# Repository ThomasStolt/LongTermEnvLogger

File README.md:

# Long Term Environment Logger

The aim of this project is to measure, store, display and evaluate the temperature in the rooms of a large building over an extended time period. This project has 2 main components:

A. The hardware of the sensor.

B. The server infrastructure to receive, store and display the measurements.

## The Hardware

1. An ultra-low power timer circuit that uses nano-Amps only when asleep and wakes up the entire circuit every approx. 5 minutes for measurement.

2. An LDO voltage regulator that regulates the incoming battery voltage from a LiIon battery to 3.3V

3. A battery voltage sensor that sends the battery voltage to the ESP8266 ADC pin with a voltage divider so that the battery voltage can be monitored.

4. The ESP8266 with a DS18B20 temperature sensor.

5. A small solar cell with a charging circuit, to keep the battery charged for as long as possible.

... and some additional mechanical and electronic components.

The ESP8266 was chosen as the microcontroller. It is versatile, very affordable, has more than enough functionality and information is easy to find.

If you think about it in detail, this project is not quite as trivial as it first appears. Some of the things to consider are:

* Runtime - How long does a single battery last?

  * As the battery-operated temperature sensors are to be distributed throughout a very large building, you want the individual sensors to run for as long as possible, so that you don't have to run around the building changing or charging batteries all the time. One option is the energy-saving mode ("DeepSleep") of the microcontroller. This would reduce the current draw during deep sleep to about 14µA. However, we want to achieve sleep current of less than 100nA! So, the normal Deep-Sleep will not do it.

* Update OTA(?)
	* It might be worth considering adding this capability. This would probably affect the runtime as well, because if we check for updates every time the circuit wakes up, it will cost runtime and energy. So, the question here is, how much runtime this would cost and is this really necessary?

* WiFi Connection Time
	* When the ESP8266 wakes up and has WiFi switched on, it draws about 70mA, which is a lot. So, all efforts need to be taken to reduce the connection time to be a short as possible.

* Power supply / battery
	* Li-Ion batteries are a good energy source for this type of project, especially the 18650 type. They are relatively inexpensive for their capacity. However, as these batteries are very sensitive to mishandling, it is important to take appropriate precautions.
		* How can you ensure that the LiIon battery will not be deep discharged?
		* How can I ensure that the LiIon battery cannot be overcharged?
		* How can I monitor the voltage of the power supply (of the LiIo battery) in order to replace or charge the battery in good time?
		* All batteries must be checked regularly for their capacity and possible health issues.

## Overview

First a short diagram for an overview:

---

## Programmer Tool

An interactive TUI (terminal user interface) that programs each sensor in two steps. Built with [Textual](https://textual.textualize.io/) for a comfortable dark-mode interface.

### Features

- Auto-detects USB serial ports (OTA/network ports filtered out) and pre-selects the right one
- Live hotplug detection — plug in the adapter and it appears immediately
- Parallel background compilation while you prepare the hardware
- Auto-selects the WiFi network from your credentials file (strongest signal)
- Two-column credentials panel — file list on the left, network config on the right; press `E` to edit
- Per-location sensor registry (`sensors_home.csv`, `sensors_school.csv`, …) — switches automatically with the selected credentials file
- Always-visible Serial Debug panel showing raw ESP output during setup-sketch read
- Adjustable baud rate selector and automatic retry loop on serial read timeout
- Full keyboard navigation — no mouse required
- Clean two-step workflow with progress feedback

### Prerequisites

- [arduino-cli](https://arduino.github.io/arduino-cli/) with the ESP8266 core installed:
  ```bash
  arduino-cli core install esp8266:esp8266
  ```
- Python 3.10+
  ```bash
  pip install -r tool/requirements.txt
  ```

### Credentials Setup

```bash
cp credentials.example.h credentials_Home.h
# Edit credentials_Home.h and fill in your SSID and password
```

You can have multiple credential files for different locations:
- `credentials_Home.h`
- `credentials_School.h`

These files are gitignored — never commit real credentials.

### Board Configuration

Edit `tool/arduino_config.py` if needed:
```python
BOARD_FQBN = "esp8266:esp8266:generic"  # change for your ESP8266 variant
```

Common FQBNs:
- `esp8266:esp8266:generic` — bare ESP-01/ESP-12 modules
- `esp8266:esp8266:nodemcuv2` — NodeMCU v2 / Lolin
- `esp8266:esp8266:d1_mini` — Wemos D1 Mini

### Running the Tool

Connect the ESP8266 via USB-TTL adapter, then:

```bash
cd tool && python3 ltl_programmer.py
```

**Keyboard shortcuts:**

| Key | Action |
|-----|--------|
| `F` | Start flash workflow |
| `R` | Refresh port list |
| `E` | Edit network config for selected credentials |
| `Q` | Quit |
| `Enter` | Confirm / Continue |

**Workflow:**

1. Select your USB-TTL adapter port (pre-selected automatically)
2. Select the credentials location (Home, School, …)
3. Press `F` to start — the tool guides you through:
   - Enter flash mode (RST + FLASH button sequence)
   - Setup sketch uploads and reads MAC address, DS18B20 address, and nearby WiFi
   - WiFi network is auto-selected from your credentials file
   - Enter a room number (1–254)
   - Production firmware compiles and uploads with all values baked in
4. Sensor is recorded in `tool/sensors_<location>.csv` (one file per credentials location)

### Flash Mode (ESP-12 / bare modules)

Bare ESP8266 modules without an auto-reset circuit require manual flash mode entry:

1. Press and hold **RST**
2. Press and hold **FLASH**
3. Release **RST**
4. Release **FLASH**

The tool will prompt you at the right moment.

### Manual Flash Fallback

If arduino-cli is not available, you can flash manually using the Arduino IDE:

1. Flash `code/LTL_setup/LTL_setup.ino` and open Serial Monitor at 115200 baud
2. Note the MAC address and DS18B20 address
3. Edit `code/LTL_sensor/LTL_sensor.ino` — replace the placeholder values
4. Copy your `credentials_<location>.h` to `credentials.h` in the same folder
5. Flash `code/LTL_sensor/LTL_sensor.ino`

### Sensor Registry

`tool/sensors_<location>.csv` tracks all programmed sensors per location (gitignored). For example, `sensors_home.csv` and `sensors_school.csv` are created automatically when you first flash a sensor using that credentials file.

| Field | Description |
|---|---|
| timestamp | When the sensor was programmed |
| room_number | Room number (also last IP octet) |
| mac_address | ESP8266 MAC address |
| ds18b20_address | DS18B20 OneWire address |
| location | Credentials location used |
| ssid | WiFi network name |
| bssid | Pinned BSSID (empty if not pinned) |
| channel | Pinned channel (empty if not pinned) |

### Battery Life Optimization

The production firmware (`code/LTL_sensor/LTL_sensor.ino`) reduces ESP8266 awake time by ~1060–1480ms per 5-minute cycle compared to the original firmware:

| Optimization | Saving |
|---|---|
| 9-bit DS18B20 resolution (±0.5°C) + async overlap | ~750ms |
| Hardcoded DS18B20 address (no bus scan) | ~10–30ms |
| Post-publish delays removed | ~300ms |
| **Total without BSSID pinning** | **~1060–1080ms** |
| Optional BSSID/channel pinning | +~200–400ms |
| **Total with BSSID pinning** | **~1260–1480ms** |

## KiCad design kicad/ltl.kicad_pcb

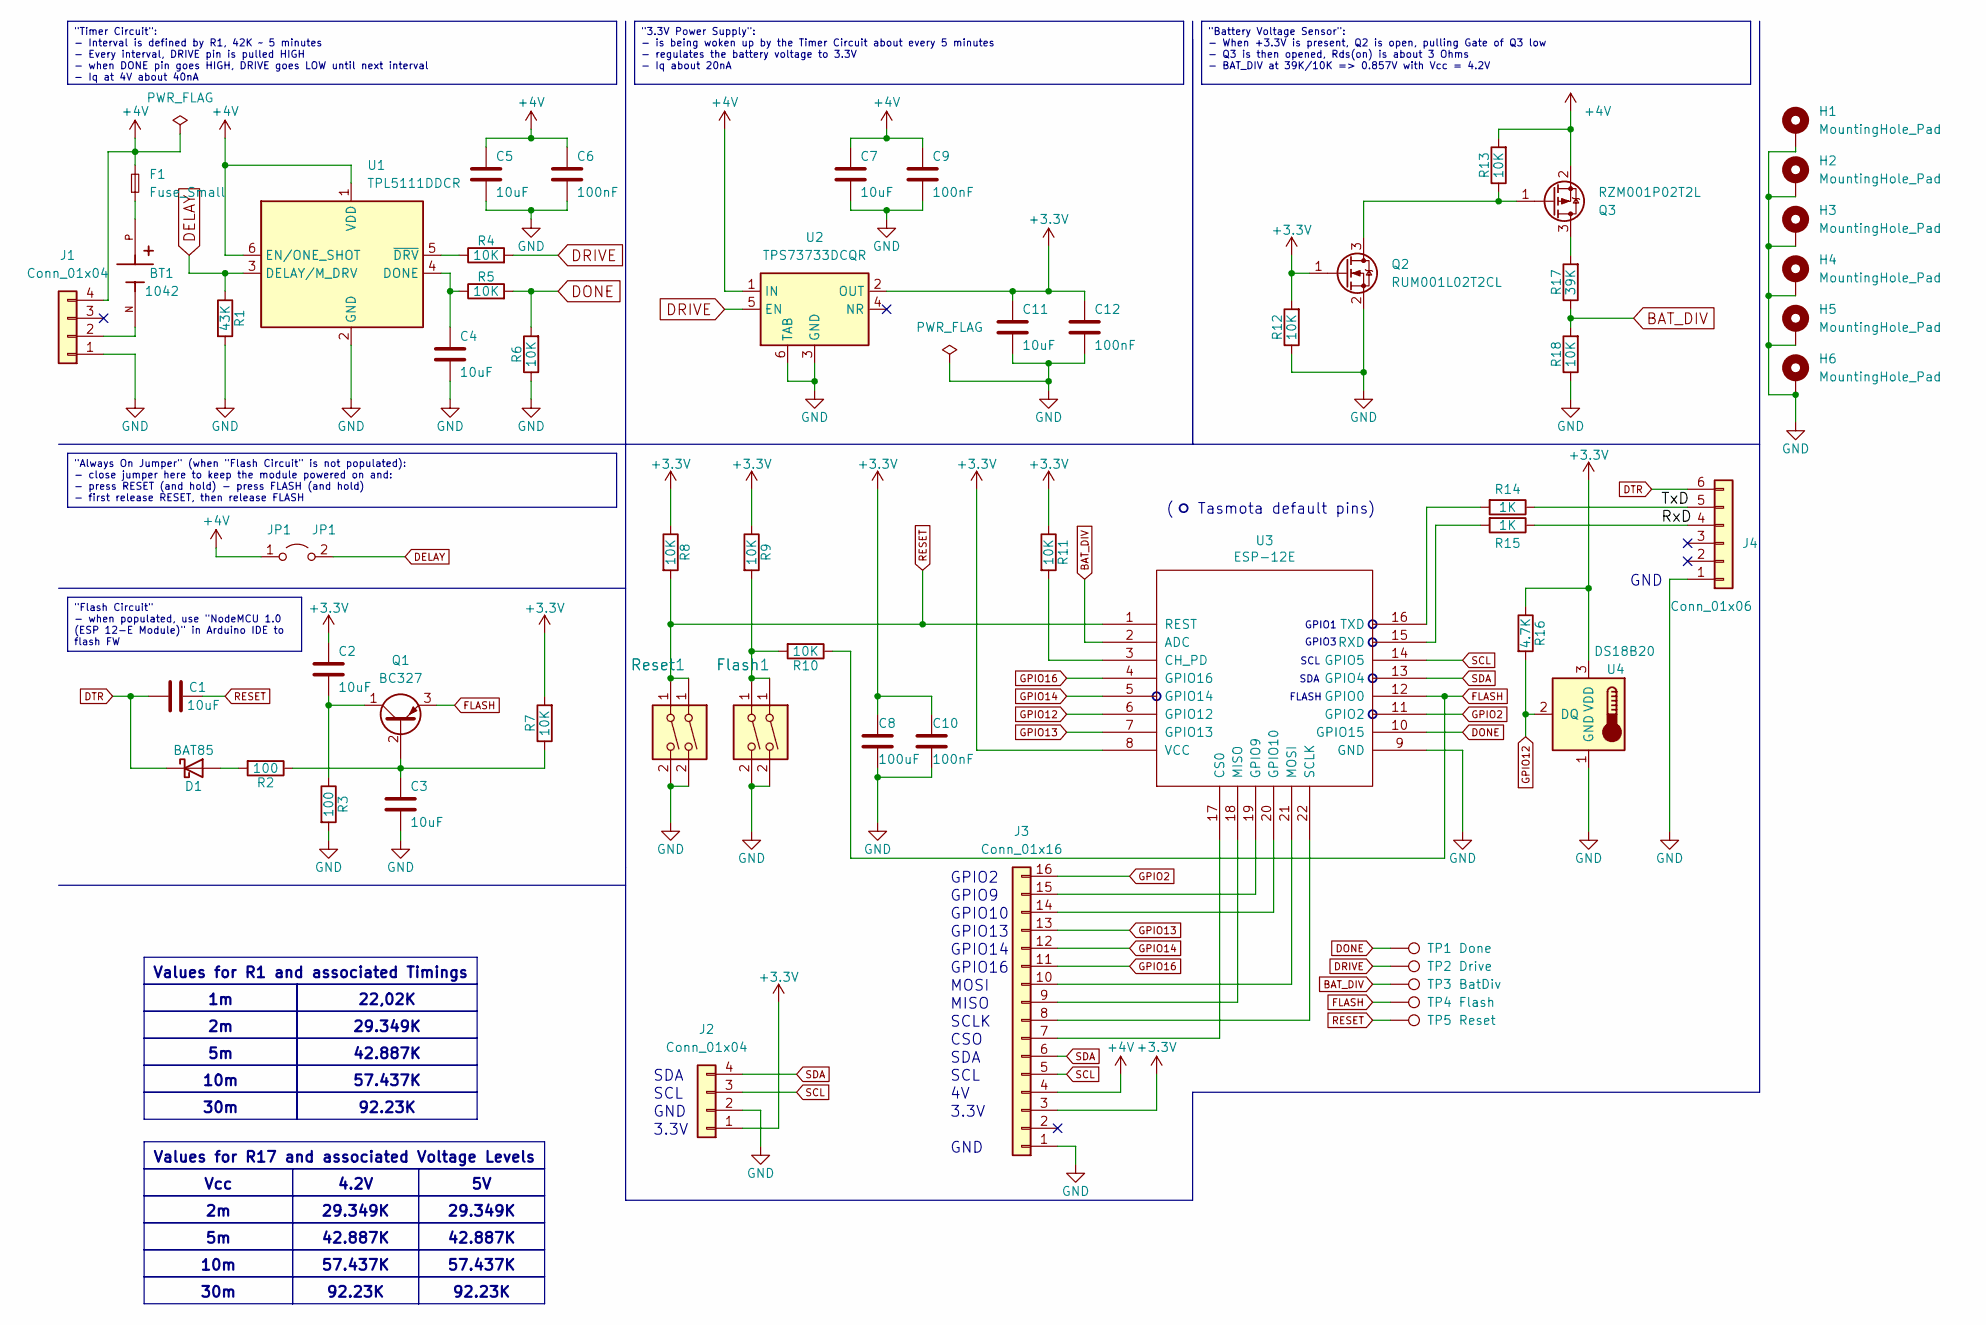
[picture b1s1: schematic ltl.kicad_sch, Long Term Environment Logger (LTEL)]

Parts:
BT1: 1042; 18650_flat; PARTREV E
C1, C2, C3: 10uF; C_1206_3216Metric
C4, C5, C7, C11: 10uF; CP_Radial_D5.0mm_P2.00mm
C6, C9, C10, C12: 100nF; C_Disc_D5.0mm_W2.5mm_P5.00mm
C8: 100uF; CP_Radial_D5.0mm_P2.00mm
D1: BAT85; D_DO-35_SOD27_P7.62mm_Horizontal
F1: Fuse_Small; Fuse_1206_3216Metric_Pad1.42x1.75mm_HandSolder
Flash1: Flash; SW_PUSH_6mm
H1, H2, H3, H4, H5, H6: MountingHole_Pad; MountingHole_3.2mm_M3_Pad_Via
J1, J2: Conn_01x04; PinHeader_1x04_P2.54mm_Vertical
J3: Conn_01x16; PinHeader_1x16_P2.54mm_Vertical
J4: Conn_01x06; PinHeader_1x06_P2.54mm_Vertical
JP1: JP1; PinHeader_1x02_P2.54mm_Vertical
Q1: BC327; TO-92_Inline_Wide
Q2: RUM001L02T2CL; SOT-723
Q3: RZM001P02T2L; SOT-723
R1: 43K; R_Axial_DIN0207_L6.3mm_D2.5mm_P10.16mm_Horizontal
R2, R3: 100; R_Axial_DIN0207_L6.3mm_D2.5mm_P10.16mm_Horizontal
R4, R5, R6, R7, R8, R9, R10, R11, R12, R13, R18: 10K; R_Axial_DIN0207_L6.3mm_D2.5mm_P10.16mm_Horizontal
R14, R15: 1K; R_Axial_DIN0207_L6.3mm_D2.5mm_P10.16mm_Horizontal
R16: 4.7K; R_Axial_DIN0207_L6.3mm_D2.5mm_P10.16mm_Horizontal
R17: 39K; R_Axial_DIN0207_L6.3mm_D2.5mm_P10.16mm_Horizontal
Reset1: Reset; SW_PUSH_6mm
TP1: Done; TestPoint_Loop_D1.80mm_Drill1.0mm_Beaded
TP2: Drive; TestPoint_Loop_D1.80mm_Drill1.0mm_Beaded
TP3: BatDiv; TestPoint_Loop_D1.80mm_Drill1.0mm_Beaded
TP4: Flash; TestPoint_Loop_D1.80mm_Drill1.0mm_Beaded
TP5: Reset; TestPoint_Loop_D1.80mm_Drill1.0mm_Beaded
U1: TPL5111DDCR; SOT-23-6
U2: TPS73733DCQR; SOT-223-6
U3: ESP-12E; ESP8266MOD
U4: DS18B20; TO-92

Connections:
+3V3: C2.1, C8.1, C10.1, C11.1, C12.1, J2.1, J3.3, Q2.1 (G), R7.2, R8.1, R9.1, R11.1, R12.2, R16.1, U2.2 (OUT), U3.8 (VCC), U4.3 (VDD)
+4V: C5.1, C6.1, C7.1, C9.1, F1.2, J1.4, J3.4, JP1.1 (A), Q3.2 (S), R13.2, U1.1 (VDD), U1.6 (EN/ONE_SHOT), U2.1 (IN)
/RxD: J4.4, R15.1
/TxD: J4.5, R14.1
BAT_DIV: R17.1, R18.2, TP3.1, U3.2 (ADC)
DELAY: JP1.2 (B), R1.1, U1.3 (DELAY/M_DRV)
DONE: R5.2, R6.2, TP1.1, U3.10 (GPIO15)
DRIVE: R4.2, TP2.1, U2.5 (EN)
DTR: C1.1, D1.1 (K), J4.6
FLASH: Q1.3 (E), R10.1, TP4.1, U3.12 (GPIO0)
GND: C3.2, C4.2, C5.2, C6.2, C7.2, C8.2, C9.2, C10.2, C11.2, C12.2, Flash1.2, H1.1, H2.1, H3.1, H4.1, H5.1, H6.1, J1.1, J2.2, J3.1, J4.1, Q2.2 (S), R1.2, R3.2, R6.1, R12.1, R18.1, Reset1.2, U1.2 (GND), U2.3 (GND), U2.6 (TAB), U3.9 (GND), U4.1 (GND)
GPIO2: J3.16, U3.11 (GPIO2)
GPIO12: R16.2, U3.6 (GPIO12), U4.2 (DQ)
GPIO13: J3.13, U3.7 (GPIO13)
GPIO14: J3.12, U3.5 (GPIO14)
GPIO16: J3.11, U3.4 (GPIO16)
unnamed: BT1.P, F1.1
unnamed: D1.2 (A), R2.2
unnamed: Flash1.1, R9.2, R10.2
unnamed: BT1.N, J1.2
unnamed: J3.7, U3.17 (CS0)
unnamed: J3.8, U3.22 (SCLK)
unnamed: J3.9, U3.18 (MISO)
unnamed: J3.10, U3.21 (MOSI)
unnamed: J3.14, U3.20 (GPIO10)
unnamed: J3.15, U3.19 (GPIO9)
unnamed: C3.1, Q1.2 (B), R2.1, R7.1
unnamed: C2.2, Q1.1 (C), R3.1
unnamed: Q2.3 (D), Q3.1 (G), R13.1
unnamed: Q3.3 (D), R17.2
unnamed: C4.1, R5.1, U1.4 (DONE)
unnamed: R4.1, U1.5 (~DRV)
unnamed: R11.2, U3.3 (CH_PD)
unnamed: R15.2, U3.15 (RXD)
unnamed: R14.2, U3.16 (TXD)
RESET: C1.2, R8.2, Reset1.1, TP5.1, U3.1 (REST)
SCL: J2.3, J3.5, U3.14 (GPIO5)
SDA: J2.4, J3.6, U3.13 (GPIO4)

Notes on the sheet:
42.887K
57.437K
92.23K
"Battery Voltage Sensor": - When +3.3V is present, Q2 is open, pulling Gate of Q3 low - Q3 is then opened, Rds(on) is about 3 Ohms - BAT_DIV at 39K/10K => 0.857V with Vcc = 4.2V
29.349K
Values for R17 and associated Voltage Levels
Vcc
"Timer Circuit": - Interval is defined by R1, 42K ~ 5 minutes - Every interval, DRIVE pin is pulled HIGH - when DONE pin goes HIGH, DRIVE goes LOW until next interval - Iq at 4V about 40nA
10m
"3.3V Power Supply": - is being woken up by the Timer Circuit about every 5 minutes - regulates the battery voltage to 3.3V - Iq about 20nA
4.2V
22,02K
"Always On Jumper" (when "Flash Circuit" is not populated): - close jumper here to keep the module powered on and: - press RESET (and hold) - press FLASH (and hold) - first release RESET, then release FLASH
30m
"Flash Circuit" - when populated, use "NodeMCU 1.0 (ESP 12-E Module)" in Arduino IDE to flash FW
Values for R1 and associated Timings
GPIO1
GPIO14
GPIO16
( Tasmota default pins)
GND
GPIO2
SDA
FLASH
GPIO9
MISO
SCL
CSO
MOSI
3.3V
GPIO10
SCLK
GPIO3
GPIO13

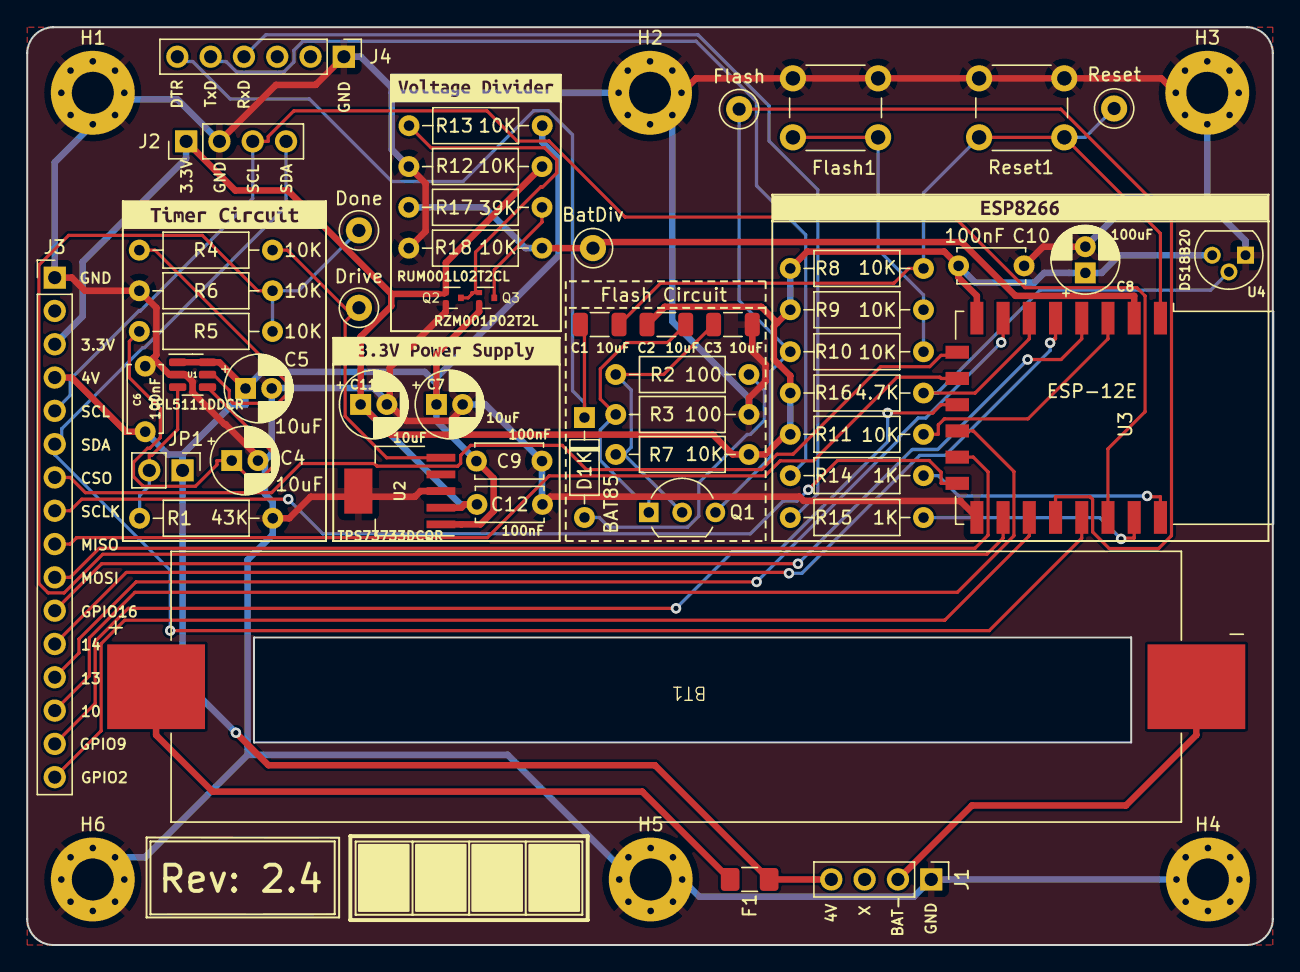
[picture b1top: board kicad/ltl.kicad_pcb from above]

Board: 2 copper layers, 95.0 x 70.0 mm, 62 parts (0 on the bottom side), 38 nets.

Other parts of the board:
kibuzzard-65AD8C40: G***; kibuzzard-65AD8C40
kibuzzard-65AD86B5: G***; kibuzzard-65AD86B5
kibuzzard-65AD8212: G***; kibuzzard-65AD8212
kibuzzard-65AD8853: G***; kibuzzard-65AD8853

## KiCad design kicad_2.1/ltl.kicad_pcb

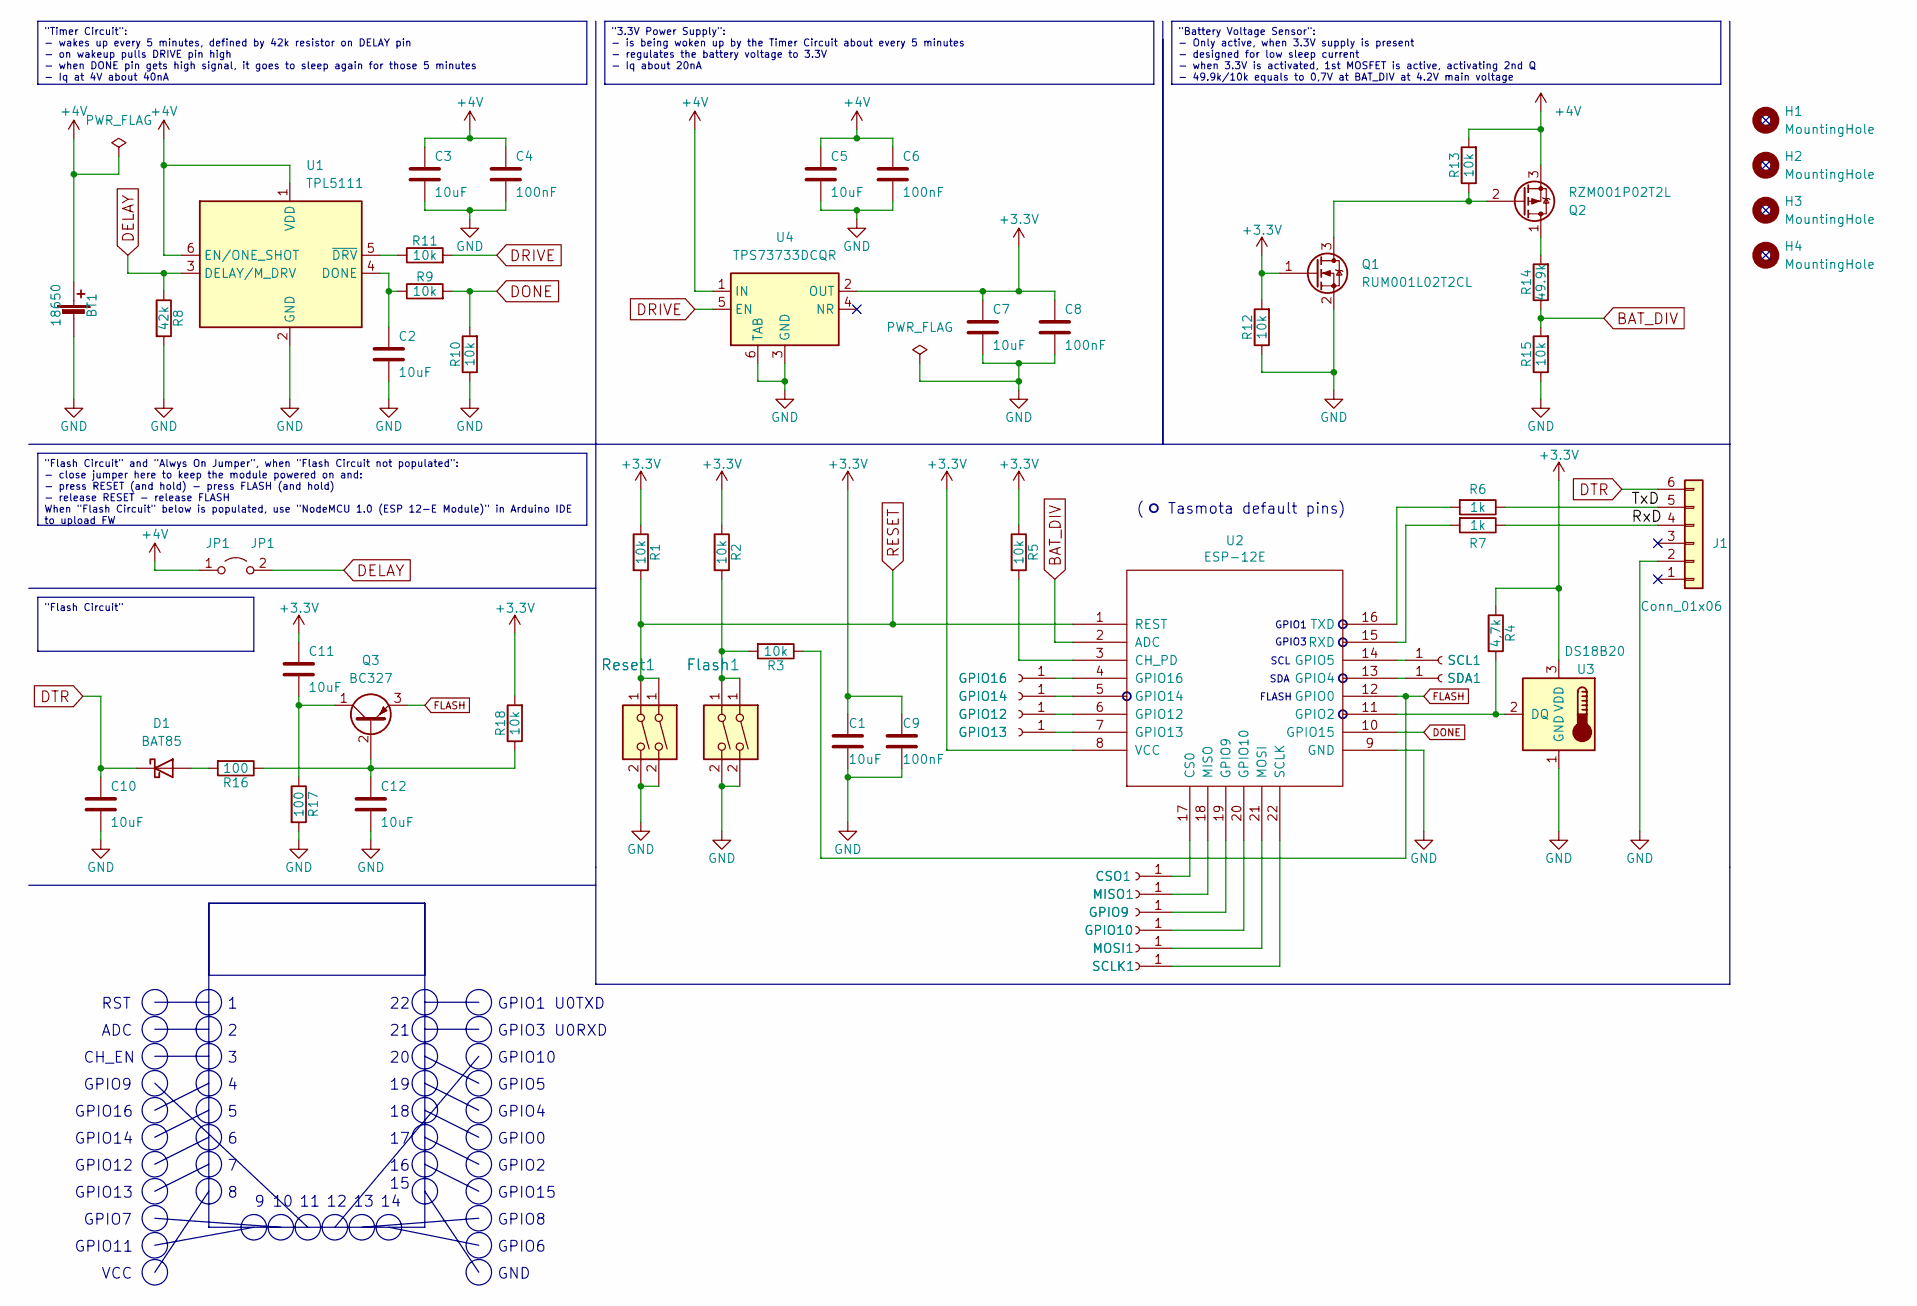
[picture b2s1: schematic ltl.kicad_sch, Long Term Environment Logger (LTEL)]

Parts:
BT1: 18650; 18650_small
C1, C2, C3, C5, C7, C11, C12: 10uF; CP_Radial_D5.0mm_P2.00mm
C4, C6, C8, C9: 100nF; C_Disc_D5.0mm_W2.5mm_P5.00mm
C10: 10uF; C_1206_3216Metric
CSO1: CSO; PinHeader_1x01_P2.54mm_Vertical
D1: BAT85; D_DO-35_SOD27_P7.62mm_Horizontal
Flash1: Flash; SW_PUSH_6mm
GPIO9: GPIO9; PinHeader_1x01_P2.54mm_Vertical
GPIO10: GPIO10; PinHeader_1x01_P2.54mm_Vertical
GPIO12: GPIO12; PinHeader_1x01_P2.54mm_Vertical
GPIO13: GPIO13; PinHeader_1x01_P2.54mm_Vertical
GPIO14: GPIO14; PinHeader_1x01_P2.54mm_Vertical
GPIO16: GPIO16; PinHeader_1x01_P2.54mm_Vertical
H1, H2, H3, H4: MountingHole; MountingHole_3.2mm_M3_Pad_Via
J1: Conn_01x06; PinHeader_1x06_P2.54mm_Horizontal
JP1: JP1; PinHeader_1x02_P2.54mm_Vertical
MISO1: MISO; PinHeader_1x01_P2.54mm_Vertical
MOSI1: MOSI; PinHeader_1x01_P2.54mm_Vertical
Q1: RUM001L02T2CL; SOT-723
Q2: RZM001P02T2L; SOT-723
Q3: BC327; TO-92_Inline
R1, R2, R3, R5, R9, R10, R11, R12, R13, R15, R18: 10k; R_Axial_DIN0411_L9.9mm_D3.6mm_P12.70mm_Horizontal
R4: 4,7k; R_Axial_DIN0411_L9.9mm_D3.6mm_P12.70mm_Horizontal
R6, R7: 1k; R_Axial_DIN0411_L9.9mm_D3.6mm_P12.70mm_Horizontal
R8: 42k; R_Axial_DIN0411_L9.9mm_D3.6mm_P12.70mm_Horizontal
R14: 49.9k; R_Axial_DIN0411_L9.9mm_D3.6mm_P12.70mm_Horizontal
R16, R17: 100; R_Axial_DIN0411_L9.9mm_D3.6mm_P12.70mm_Horizontal
Reset1: Reset; SW_PUSH_6mm
SCL1: SCL; PinHeader_1x01_P2.54mm_Vertical
SCLK1: SCLK; PinHeader_1x01_P2.54mm_Vertical
SDA1: SDA; PinHeader_1x01_P2.54mm_Vertical
U1: TPL5111; SOT-23-6
U2: ESP-12E
U3: DS18B20; TO-92
U4: TPS73733DCQR; SOT-223-6

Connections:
+3V3: C1.1, C7.1, C8.1, C9.1, C11.1, Q1.1 (G), R1.1, R2.1, R4.1, R5.1, R12.2, R18.2, U2.8 (VCC), U3.3 (VDD), U4.2 (OUT)
+4V: BT1.1 (+), C3.1, C4.1, C5.1, C6.1, JP1.1 (A), Q2.3 (S), R13.2, U1.1 (VDD), U1.6 (EN/ONE_SHOT), U4.1 (IN)
/RxD: J1.4, R7.1
/TxD: J1.5, R6.1
BAT_DIV: R14.1, R15.2, U2.2 (ADC)
DELAY: JP1.2 (B), R8.1, U1.3 (DELAY/M_DRV)
DONE: R9.2, R10.2, U2.10 (GPIO15)
DRIVE: R11.2, U4.5 (EN)
DTR: C10.1, D1.1 (K), J1.6
FLASH: Q3.3 (E), R3.1, U2.12 (GPIO0)
GND: BT1.2 (-), C1.2, C2.2, C3.2, C4.2, C5.2, C6.2, C7.2, C8.2, C9.2, C10.2, C12.2, Flash1.2, J1.2, Q1.2 (S), R8.2, R10.1, R12.1, R15.1, R17.2, Reset1.2, U1.2 (GND), U2.9 (GND), U3.1 (GND), U4.3 (GND), U4.6 (TAB)
unnamed: CSO1.1, U2.17 (CS0)
unnamed: D1.2 (A), R16.2
unnamed: Flash1.1, R2.2, R3.2
unnamed: GPIO9.1, U2.19 (GPIO9)
unnamed: GPIO10.1, U2.20 (GPIO10)
unnamed: GPIO12.1, U2.6 (GPIO12)
unnamed: GPIO13.1, U2.7 (GPIO13)
unnamed: GPIO14.1, U2.5 (GPIO14)
unnamed: GPIO16.1, U2.4 (GPIO16)
unnamed: MISO1.1, U2.18 (MISO)
unnamed: MOSI1.1, U2.21 (MOSI)
unnamed: Q1.3 (D), Q2.2 (G), R13.1
unnamed: Q2.1 (D), R14.2
unnamed: C12.1, Q3.2 (B), R16.1, R18.1
unnamed: C11.2, Q3.1 (C), R17.1
unnamed: SCL1.1, U2.14 (GPIO5)
unnamed: SCLK1.1, U2.22 (SCLK)
unnamed: SDA1.1, U2.13 (GPIO4)
unnamed: C2.1, R9.1, U1.4 (DONE)
unnamed: R11.1, U1.5 (~DRV)
unnamed: R5.2, U2.3 (CH_PD)
unnamed: R4.2, U2.11 (GPIO2), U3.2 (DQ)
unnamed: R7.2, U2.15 (RXD)
unnamed: R6.2, U2.16 (TXD)
RESET: R1.2, Reset1.1, U2.1 (REST)

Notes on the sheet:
"Battery Voltage Sensor": - Only active, when 3.3V supply is present - designed for low sleep current - when 3.3V is activated, 1st MOSFET is active, activating 2nd Q - 49.9k/10k equals to 0,7V at BAT_DIV at 4.2V main voltage
"Timer Circuit": - wakes up every 5 minutes, defined by 42k resistor on DELAY pin - on wakeup pulls DRIVE pin high - when DONE pin gets high signal, it goes to sleep again for those 5 minutes - Iq at 4V about 40nA
"3.3V Power Supply": - is being woken up by the Timer Circuit about every 5 minutes - regulates the battery voltage to 3.3V - Iq about 20nA
"Flash Circuit" and "Alwys On Jumper", when "Flash Circuit not populated": - close jumper here to keep the module powered on and: - press RESET (and hold) - press FLASH (and hold) - release RESET - release FLASH When "Flash Circuit" below is populated, use "NodeMCU 1.0 (ESP 12-E Module)" in Arduino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
"Flash Circuit"
GPIO1
GPIO1 U0TXD
GPIO8
GPIO4
GPIO13
( Tasmota default pins)
GPIO9
GPIO7
GPIO16
FLASH
GND
GPIO6
GPIO0
SCL
SDA
GPIO15
GPIO10
CH_EN
GPIO14
VCC
GPIO11
GPIO5
GPIO3
GPIO3 U0RXD
GPIO12
ADC
RST
GPIO2

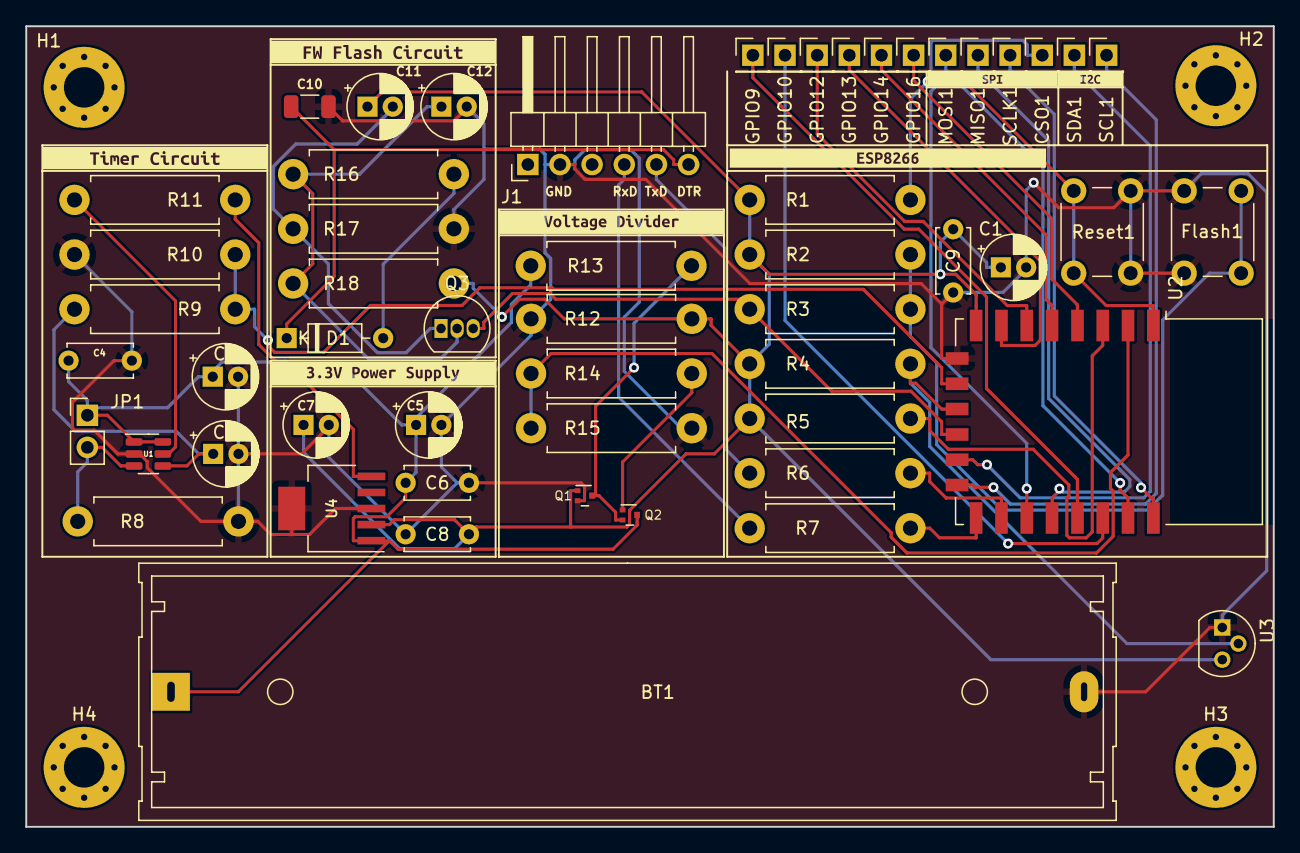
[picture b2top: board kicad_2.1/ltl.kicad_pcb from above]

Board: 2 copper layers, 98.6 x 63.2 mm, 66 parts (0 on the bottom side), 36 nets.

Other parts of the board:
kibuzzard-659AB4FF: G***; kibuzzard-659AB4FF
kibuzzard-65989B2E: G***; kibuzzard-65989B2E
kibuzzard-65989B49: G***; kibuzzard-65989B49
kibuzzard-65989BDF: G***; kibuzzard-65989BDF
kibuzzard-65989638: G***; kibuzzard-65989638
kibuzzard-65989978: G***; kibuzzard-65989978
kibuzzard-65991234: G***; kibuzzard-65991234

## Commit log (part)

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2018-02-01 Second commit
2018-02-01 added PDF directory
2018-02-01 Changes in scope, not limited to temperature only
2018-04-02 some minor changes
2020-03-10 Test
2020-03-12 Kleinere Änderungen
2020-03-15 letzte Änderungen
2020-03-15 code hinzugefügt
2020-03-17 Added Solution Overview 1
2020-03-17 Added Solution Overview 2
2020-03-19 Zweite Revision der Leiterplatte, mehrere Fehler beseitigt: - Schalter Symbol und Footprint haben nicht übereingestimmt (Nummerierung), dadurch nur mit Schwierigkeiten einsetzbar (3 Leiterbahnen müss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
    Desweiteren noch ein aktualisiertes 3D Image der Leiterplatte hinzugefügt.
    Anonsten ist der erste Prototyp funktionsfähig :)
2020-03-19 Schaltplan aktualisiert
2020-03-26 Viele Änderungen, siehe Wiki
2020-03-26 3D Bild für Rev 1.2
2020-03-26 Anpassungen im README.md und Schaltplanaktualisierung
2020-03-30 Rev. 1.1 angekommen
2020-03-30 Letzte Fehler
2020-06-25 ch ch ch changes
2020-06-25 ch ch ch changes2
2020-06-25 ch ch ch changes3
2023-12-12 Added timer and voltage regulator for low power requirements
2023-12-27 Lots of added features and bug fixes
2024-01-09 Latest PCB version, sent for production
2024-02-02 Updated PCB to Revision 2.2
2024-02-02 Added PCB 3D image
2024-02-02 Added 2.1 Build picture
2024-03-06 Created .gitignore and move credentials to credentials.h
2024-03-10 A couple of addictions
2024-03-10 Updated architecture images
2024-03-10 Removed unused files
2024-03-10 Updated images
2024-03-10 Last updates
2024-03-13 Updated last image
2024-03-13 Added UART adapter image
2024-03-13 Added Entladeverlauf
2024-03-13 Added Charger Picture
2024-03-13 Added 18650 images
2024-03-13 Added INR18650-30Q discharge image
2024-03-13 Update images
2024-03-16 Updated code to account for WiFi and MQTT broker outages and several other cleanups
2025-05-15 Few changes in the README
2025-05-15 Additional changes
2026-03-22 feat: add project scaffolding for programmer tool
2026-03-22 feat: add optimized LTL_sensor firmware template with async DS18B20 and placeholder tokens
2026-03-22 feat: add LTL_setup sketch for hardware discovery
2026-03-22 feat: add tool foundation — arduino_config.py and ltl_programmer.py skeleton
2026-03-22 feat: add serial output parser with tests
2026-03-22 feat: add DS18B20 and BSSID address formatter utilities with tests
2026-03-22 feat: add template substitution with tests
2026-03-22 feat: add CSV handler and credentials finder with tests
2026-03-22 feat: add port detection and credentials selection UI
2026-03-22 feat: add arduino-cli flash and serial data reader
2026-03-22 feat: add WiFi display and configuration input UI
2026-03-22 feat: add production firmware builder and complete main() workflow
2026-03-22 docs: add programmer tool documentation to README
2026-03-22 chore: resolve .gitignore merge conflict
2026-03-23 feat: add network config fields to credentials.example.h
2026-03-23 fix: add length validation to format_bssid_c_array with test
2026-03-23 feat: replace hardcoded network values with credentials.h constants
